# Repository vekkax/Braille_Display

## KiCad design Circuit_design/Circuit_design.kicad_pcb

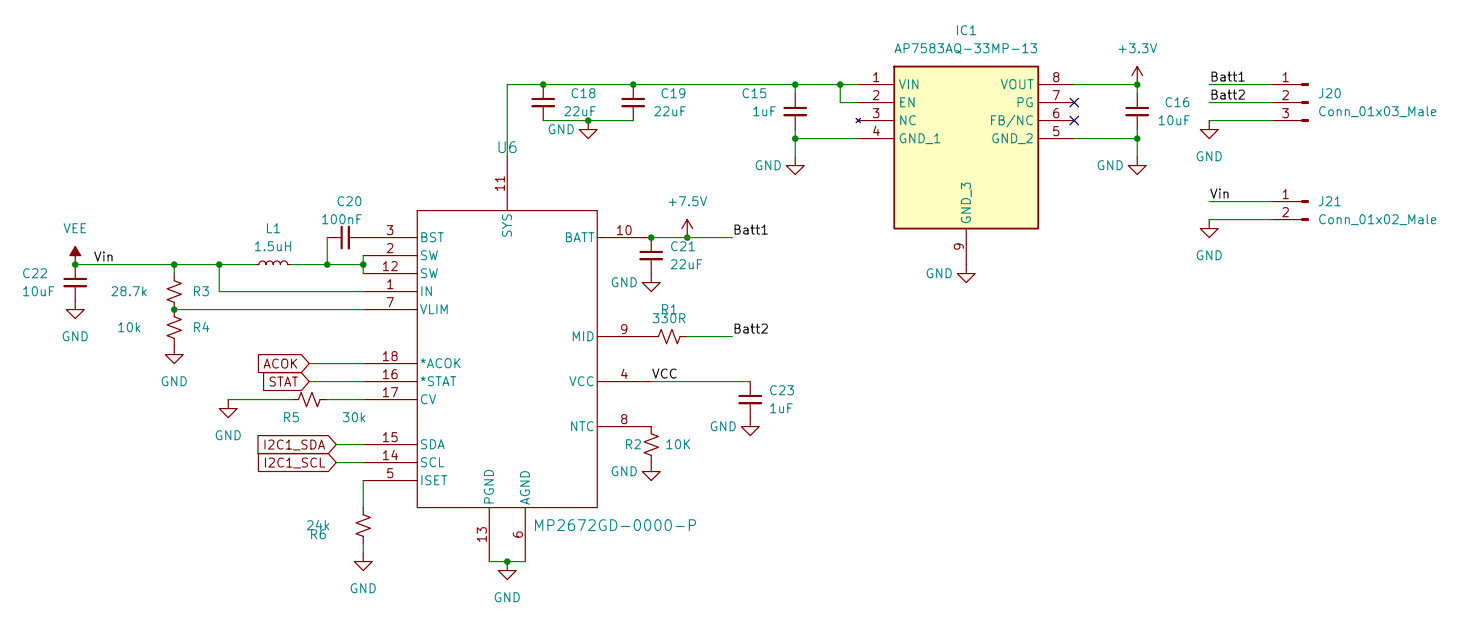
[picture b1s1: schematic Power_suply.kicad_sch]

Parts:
C15, C23: 1uF; C_0805_2012Metric_Pad1.18x1.45mm_HandSolder
C16, C22: 10uF; C_0805_2012Metric_Pad1.18x1.45mm_HandSolder
C18, C19, C21: 22uF; C_0805_2012Metric_Pad1.18x1.45mm_HandSolder
C20: 100nF; C_0805_2012Metric_Pad1.18x1.45mm_HandSolder
IC1: AP7583AQ-33MP-13; SOP65P490X110-9N; Mouser Part Number 621-AP7583AQ-33MP-13
J20: Conn_01x03_Male; JST_PH_S3B-PH-K_1x03_P2.00mm_Horizontal
J21: Conn_01x02_Male; JST_PH_S2B-PH-K_1x02_P2.00mm_Horizontal
L1: 1.5uH; L_Vishay_IHLP-2525
R1: 330R; R_0805_2012Metric_Pad1.20x1.40mm_HandSolder
R2: 10K; R_0805_2012Metric_Pad1.20x1.40mm_HandSolder
R3: 28.7k; R_0805_2012Metric_Pad1.20x1.40mm_HandSolder
R4: 10k; R_0805_2012Metric_Pad1.20x1.40mm_HandSolder
R5: 30k; R_0805_2012Metric_Pad1.20x1.40mm_HandSolder
R6: 24k; R_0805_2012Metric_Pad1.20x1.40mm_HandSolder
U6: MP2672GD-0000-P; QFN-18_2MMx3MM_MP2672_MNP_MPS

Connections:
+3.3V: C16.1, IC1.8 (VOUT); also elsewhere on the board
+7.5V: C21.1, J20.1, U6.10 (BATT); also elsewhere on the board
/Power_suply/Batt2: J20.2, R1.2
/Power_suply/VCC: C23.1, U6.4 (VCC)
ACOK: U6.18 (*ACOK)
GND: C15.2, C16.2, C18.2, C19.2, C21.2, C22.2, C23.2, IC1.4 (GND_1), IC1.5 (GND_2), IC1.9 (GND_3), J20.3, J21.2, R2.2, R4.1, R5.1, R6.1, U6.6 (AGND), U6.13 (PGND); also elsewhere on the board
I2C1_SCL: U6.14 (SCL); also elsewhere on the board
I2C1_SDA: U6.15 (SDA); also elsewhere on the board
unnamed: C20.1, L1.2, U6.2 (SW), U6.12 (SW)
unnamed: C15.1, C18.1, C19.1, IC1.1 (VIN), IC1.2 (EN), U6.11 (SYS)
unnamed: C20.2, U6.3 (BST)
unnamed: R5.2, U6.17 (CV)
unnamed: R6.2, U6.5 (ISET)
unnamed: R1.1, U6.9 (MID)
unnamed: R2.1, U6.8 (NTC)
unnamed: R3.1, R4.2, U6.7 (VLIM)
STAT: U6.16 (*STAT)
VEE: C22.1, J21.1, L1.1, R3.2, U6.1 (IN)

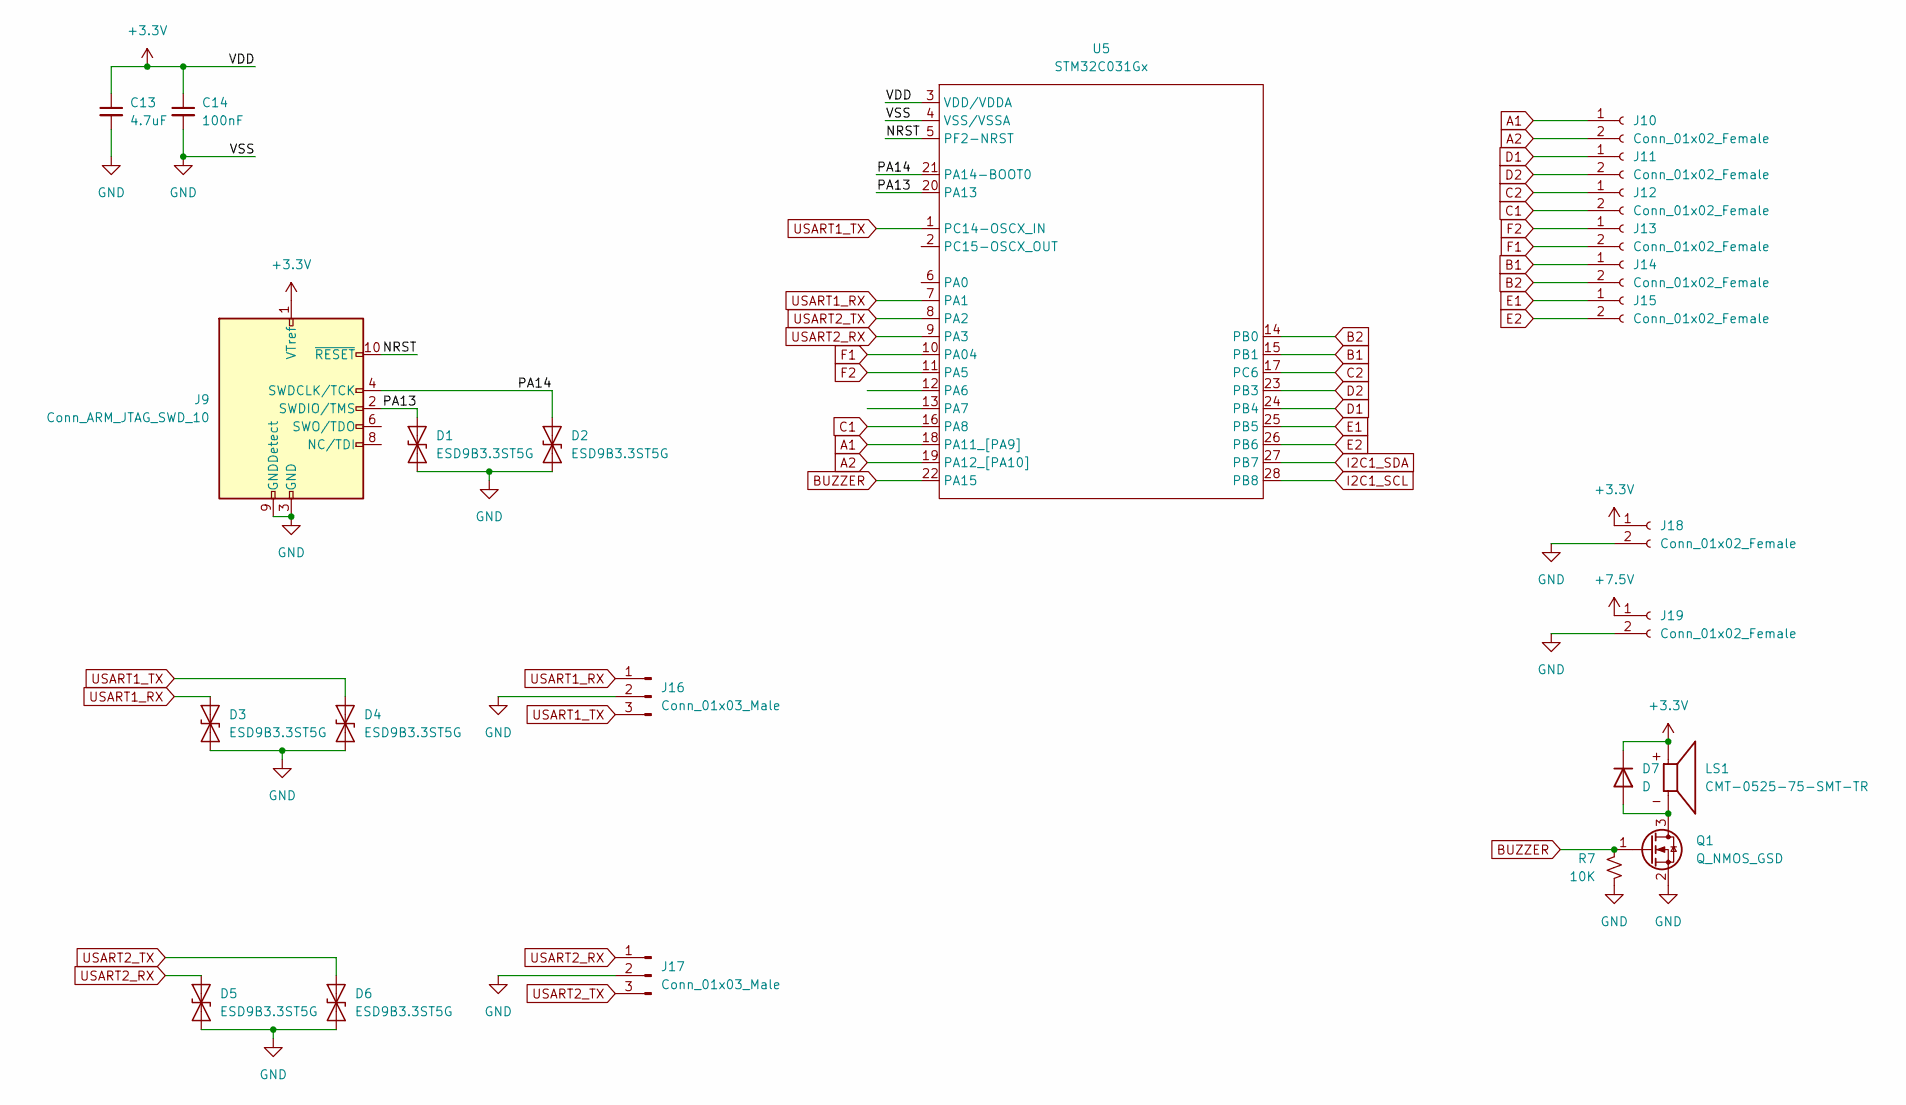
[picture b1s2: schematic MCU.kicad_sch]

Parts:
C13: 4.7uF; C_0603_1608Metric_Pad1.08x0.95mm_HandSolder
C14: 100nF; C_0603_1608Metric_Pad1.08x0.95mm_HandSolder
D1, D2, D3, D4, D5, D6: ESD9B3.3ST5G; D_SOD-923
D7: D; D_SOD-323
J9: Conn_ARM_JTAG_SWD_10; PinHeader_2x05_P1.27mm_Vertical
J10, J11, J12, J13, J14, J15, J18, J19: Conn_01x02_Female; PinSocket_1x02_P2.54mm_Vertical
J16, J17: Conn_01x03_Male; JST_PH_S3B-PH-K_1x03_P2.00mm_Horizontal
LS1: CMT-0525-75-SMT-TR; XDCR_CMT-0525-75-SMT-TR; PARTREV 1.0
Q1: Q_NMOS_GSD; SOT-23-3
R7: 10K; R_0805_2012Metric_Pad1.20x1.40mm_HandSolder
U5: STM32C031Gx; QFN50P400X400X60-28N

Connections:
+3.3V: C13.1, C14.1, D7.1 (K), J9.1 (VTref), J18.1, LS1.P, U5.3 (VDD/VDDA); also elsewhere on the board
+7.5V: J19.1; also elsewhere on the board
/MCU/NRST: J9.10 (~RESET), U5.5 (PF2-NRST)
/MCU/PA13: D1.2 (A2), J9.2 (SWDIO/TMS), U5.20 (PA13)
/MCU/PA14: D2.2 (A2), J9.4 (SWDCLK/TCK), U5.21 (PA14-BOOT0)
A1: J10.1, U5.18 (PA11_[PA9]); also elsewhere on the board
A2: J10.2, U5.19 (PA12_[PA10]); also elsewhere on the board
B1: J14.1, U5.15 (PB1); also elsewhere on the board
B2: J14.2, U5.14 (PB0); also elsewhere on the board
BUZZER: Q1.1 (G), R7.1, U5.22 (PA15)
C1: J12.2, U5.16 (PA8); also elsewhere on the board
C2: J12.1, U5.17 (PC6); also elsewhere on the board
D1: J11.1, U5.24 (PB4); also elsewhere on the board
D2: J11.2, U5.23 (PB3); also elsewhere on the board
E1: J15.1, U5.25 (PB5); also elsewhere on the board
E2: J15.2, U5.26 (PB6); also elsewhere on the board
F1: J13.2, U5.10 (PA04); also elsewhere on the board
F2: J13.1, U5.11 (PA5); also elsewhere on the board
GND: C13.2, C14.2, D1.1 (A1), D2.1 (A1), D3.1 (A1), D4.1 (A1), D5.1 (A1), D6.1 (A1), J9.3 (GND), J9.5 (GND), J9.9 (GNDDetect), J16.2, J17.2, J18.2, J19.2, Q1.2 (S), R7.2, U5.4 (VSS/VSSA); also elsewhere on the board
I2C1_SCL: U5.28 (PB8); also elsewhere on the board
I2C1_SDA: U5.27 (PB7); also elsewhere on the board
unnamed: D7.2 (A), LS1.N, Q1.3 (D)
USART1_RX: D3.2 (A2), J16.1, U5.7 (PA1)
USART1_TX: D4.2 (A2), J16.3, U5.1 (PC14-OSCX_IN)
USART2_RX: D5.2 (A2), J17.1, U5.9 (PA3)
USART2_TX: D6.2 (A2), J17.3, U5.8 (PA2)

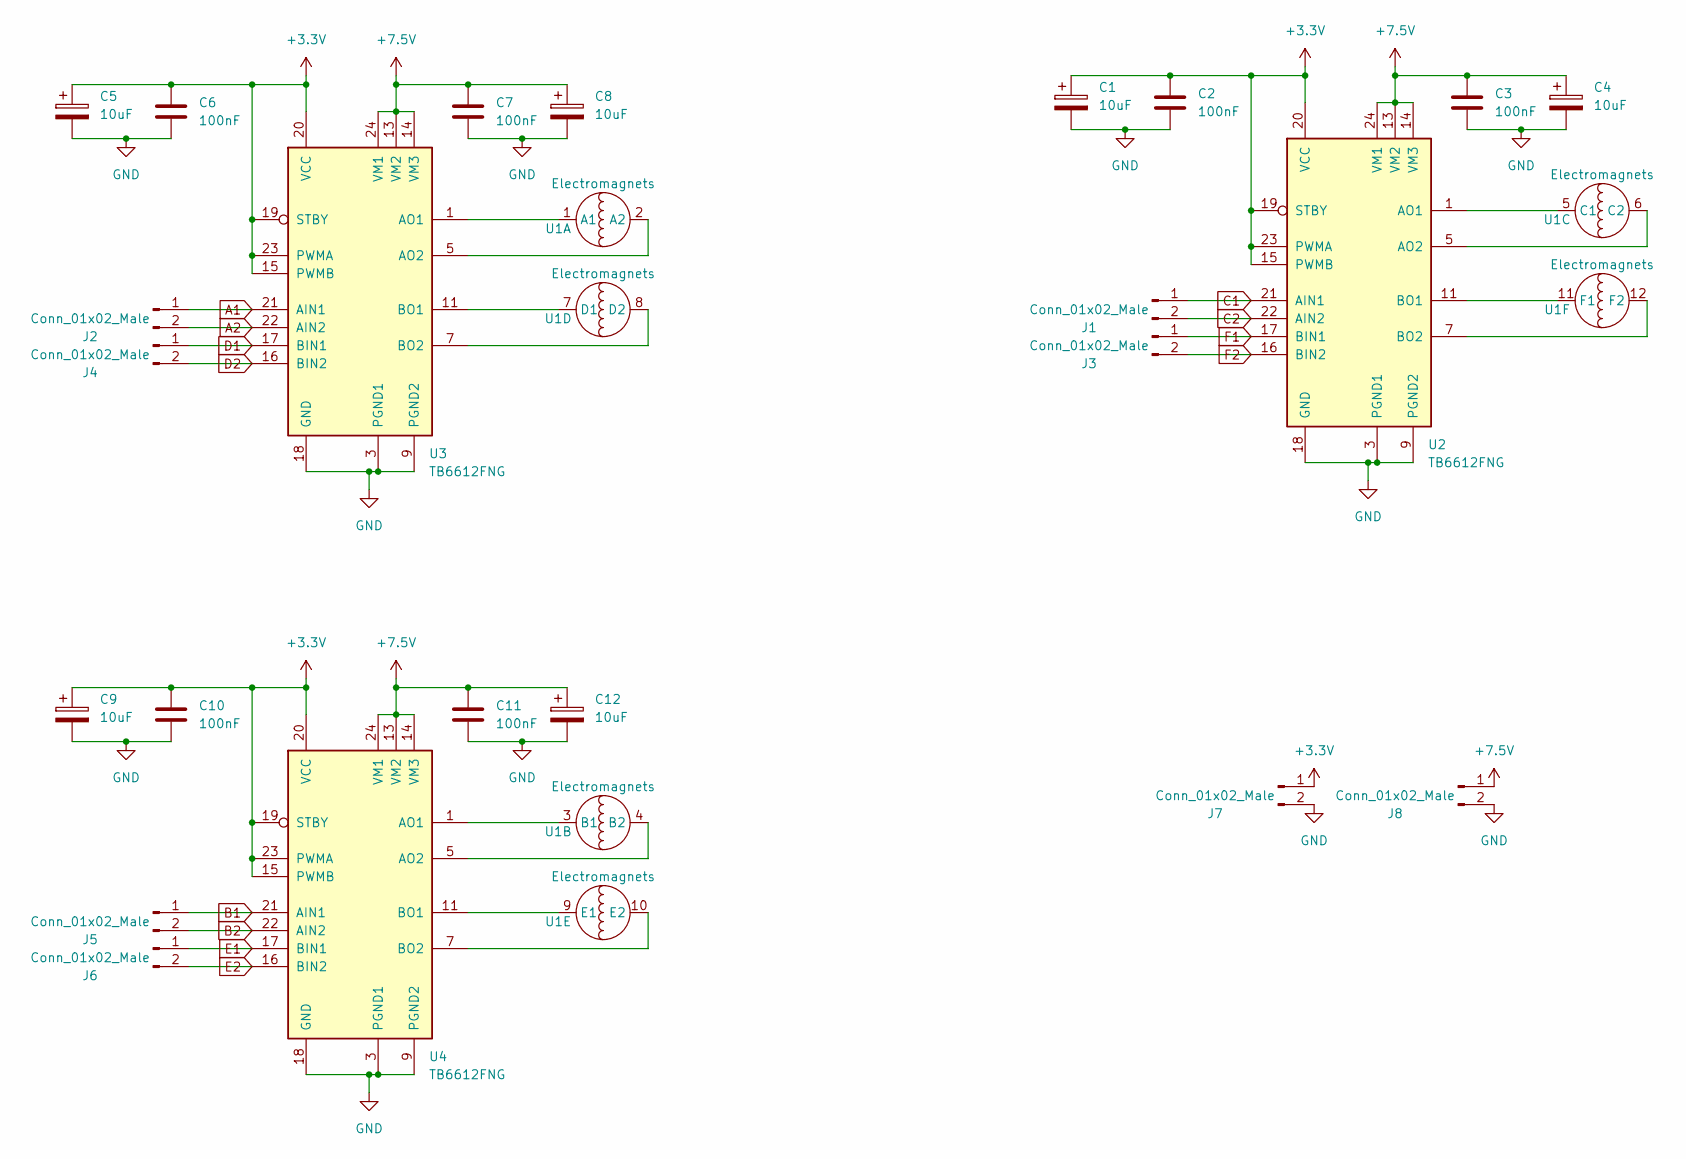
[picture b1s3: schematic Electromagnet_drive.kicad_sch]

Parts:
C1, C4, C5, C8, C9, C12: 10uF; C_0603_1608Metric_Pad1.08x0.95mm_HandSolder
C2, C3, C6, C7, C10, C11: 100nF; C_0603_1608Metric_Pad1.08x0.95mm_HandSolder
J1, J2, J3, J4, J5, J6, J7, J8: Conn_01x02_Male; PinHeader_1x02_P2.54mm_Vertical
U1: Electromagnets
U2, U3, U4: TB6612FNG; SSOP-24_5.3x8.2mm_P0.65mm

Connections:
+3.3V: C1.1, C2.1, C5.1, C6.1, C9.1, C10.1, J7.1, U2.15 (PWMB), U2.19 (STBY), U2.20 (VCC), U2.23 (PWMA), U3.15 (PWMB), U3.19 (STBY), U3.20 (VCC), U3.23 (PWMA), U4.15 (PWMB), U4.19 (STBY), U4.20 (VCC), U4.23 (PWMA); also elsewhere on the board
+7.5V: C3.1, C4.1, C7.1, C8.1, C11.1, C12.1, J8.1, U2.13 (VM2), U2.14 (VM3), U2.24 (VM1), U3.13 (VM2), U3.14 (VM3), U3.24 (VM1), U4.13 (VM2), U4.14 (VM3), U4.24 (VM1); also elsewhere on the board
A1: J2.1, U3.21 (AIN1); also elsewhere on the board
A2: J2.2, U3.22 (AIN2); also elsewhere on the board
B1: J5.1, U4.21 (AIN1); also elsewhere on the board
B2: J5.2, U4.22 (AIN2); also elsewhere on the board
C1: J1.1, U2.21 (AIN1); also elsewhere on the board
C2: J1.2, U2.22 (AIN2); also elsewhere on the board
D1: J4.1, U3.17 (BIN1); also elsewhere on the board
D2: J4.2, U3.16 (BIN2); also elsewhere on the board
E1: J6.1, U4.17 (BIN1); also elsewhere on the board
E2: J6.2, U4.16 (BIN2); also elsewhere on the board
F1: J3.1, U2.17 (BIN1); also elsewhere on the board
F2: J3.2, U2.16 (BIN2); also elsewhere on the board
GND: C1.2, C2.2, C3.2, C4.2, C5.2, C6.2, C7.2, C8.2, C9.2, C10.2, C11.2, C12.2, J7.2, J8.2, U2.3 (PGND1), U2.4 (PGND1), U2.9 (PGND2), U2.10 (PGND2), U2.18 (GND), U3.3 (PGND1), U3.4 (PGND1), U3.9 (PGND2), U3.10 (PGND2), U3.18 (GND), U4.3 (PGND1), U4.4 (PGND1), U4.9 (PGND2), U4.10 (PGND2), U4.18 (GND); also elsewhere on the board
unnamed: U1.1 (A1), U3.1 (AO1), U3.2 (AO1)
unnamed: U1.2 (A2), U3.5 (AO2), U3.6 (AO2)
unnamed: U1.3 (B1), U4.1 (AO1), U4.2 (AO1)
unnamed: U1.4 (B2), U4.5 (AO2), U4.6 (AO2)
unnamed: U1.5 (C1), U2.1 (AO1), U2.2 (AO1)
unnamed: U1.6 (C2), U2.5 (AO2), U2.6 (AO2)
unnamed: U1.7 (D1), U3.11 (BO1), U3.12 (BO1)
unnamed: U1.8 (D2), U3.7 (BO2), U3.8 (BO2)
unnamed: U1.9 (E1), U4.11 (BO1), U4.12 (BO1)
unnamed: U1.10 (E2), U4.7 (BO2), U4.8 (BO2)
unnamed: U1.11 (F1), U2.11 (BO1), U2.12 (BO1)
unnamed: U1.12 (F2), U2.7 (BO2), U2.8 (BO2)

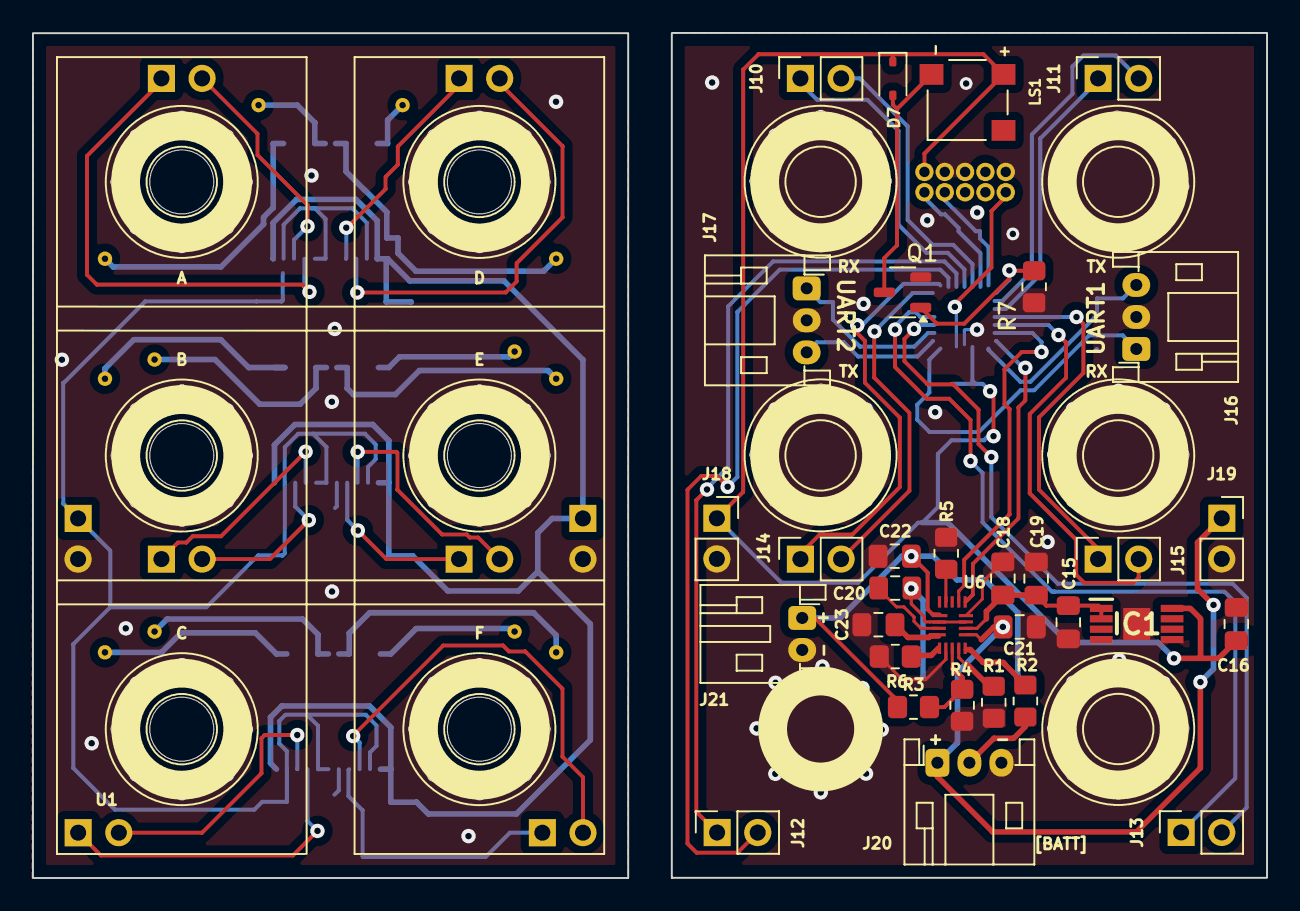
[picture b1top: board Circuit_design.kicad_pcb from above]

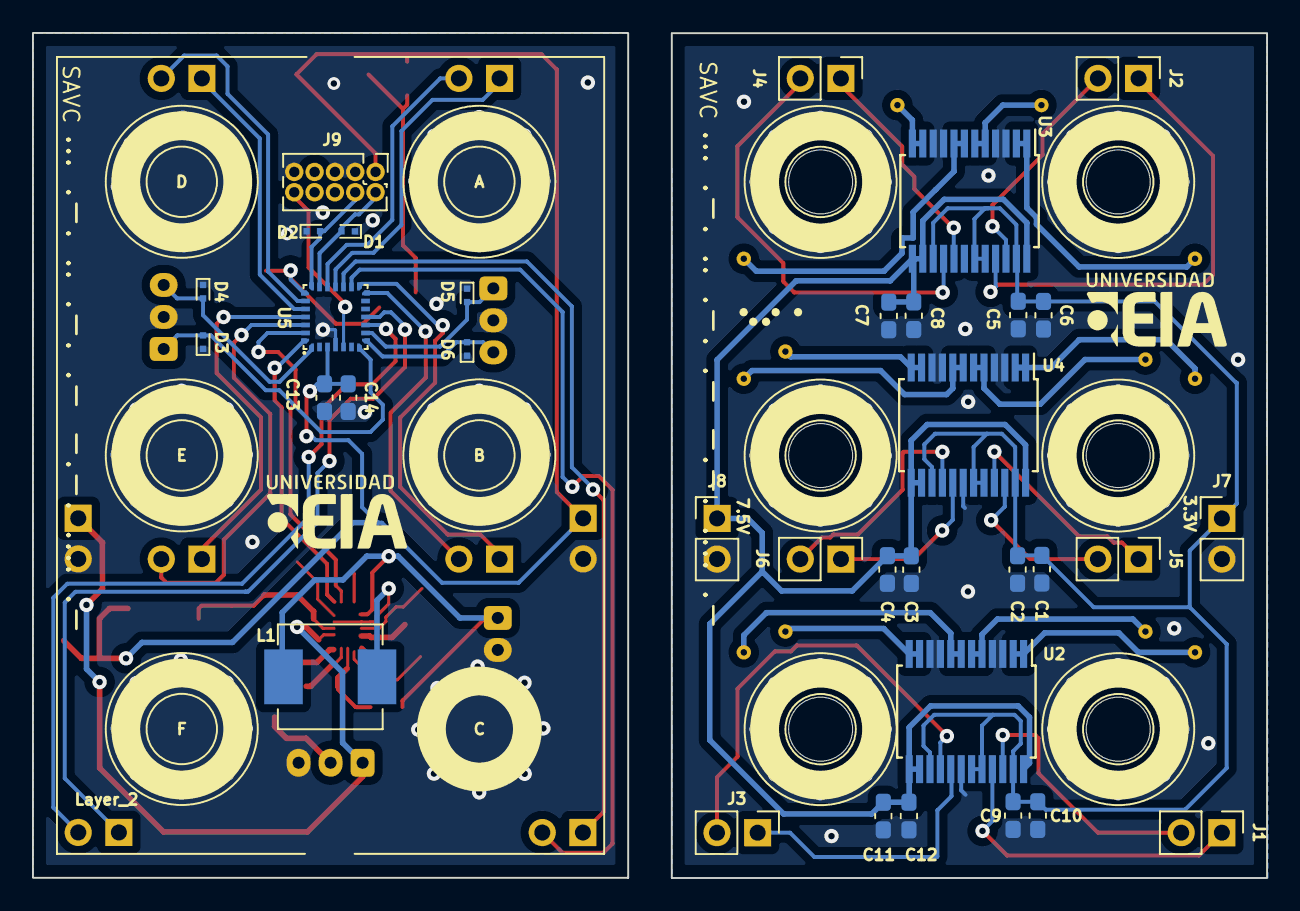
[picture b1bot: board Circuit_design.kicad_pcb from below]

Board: 2 copper layers, 77.1 x 52.8 mm, 68 parts (35 on the bottom side), 49 nets.

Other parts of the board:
Layer_2: Electromagnets_Layer_2

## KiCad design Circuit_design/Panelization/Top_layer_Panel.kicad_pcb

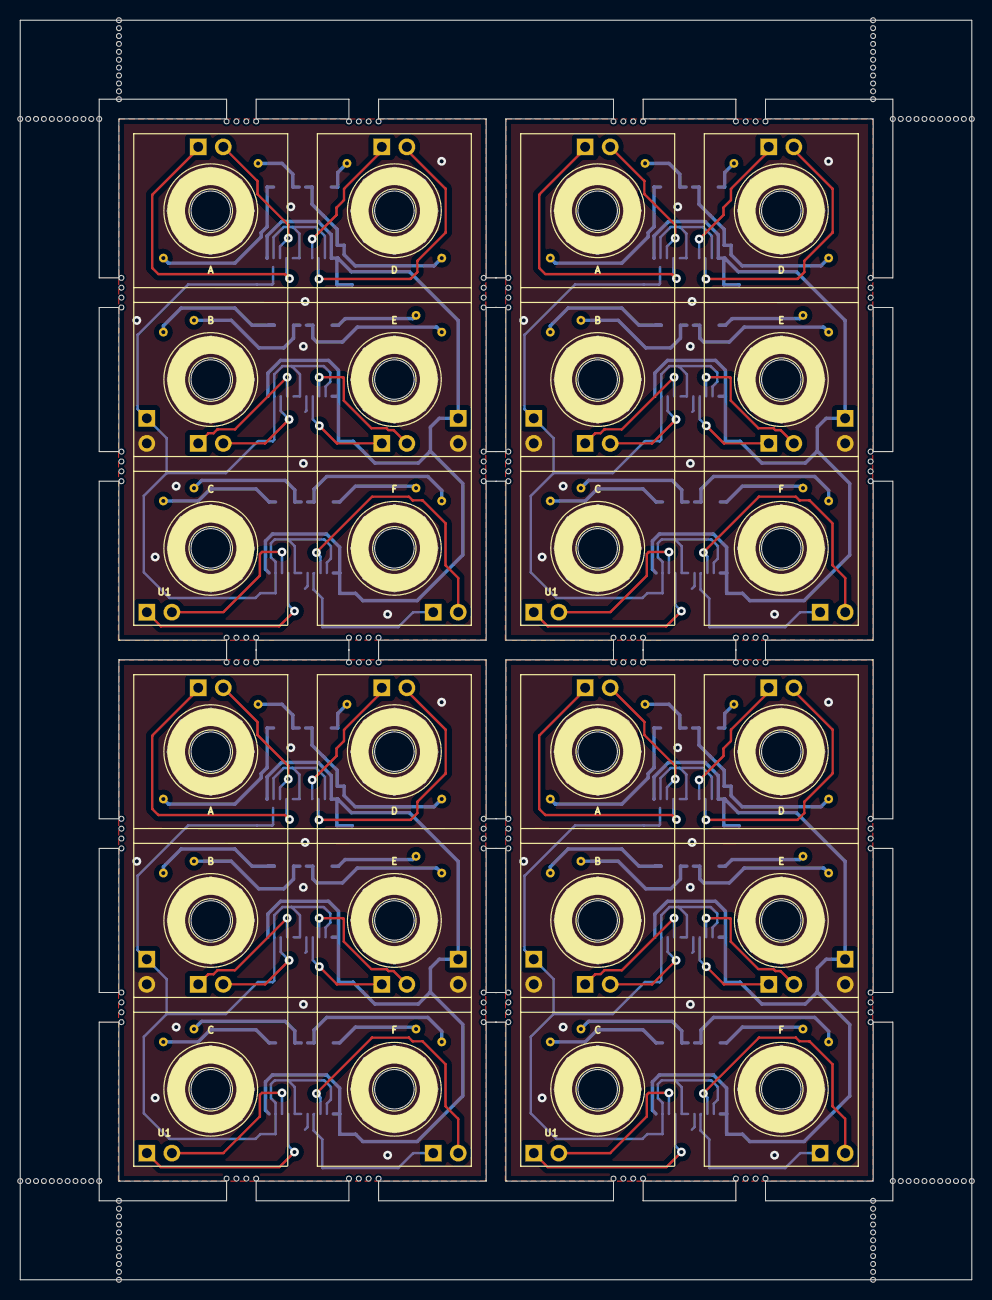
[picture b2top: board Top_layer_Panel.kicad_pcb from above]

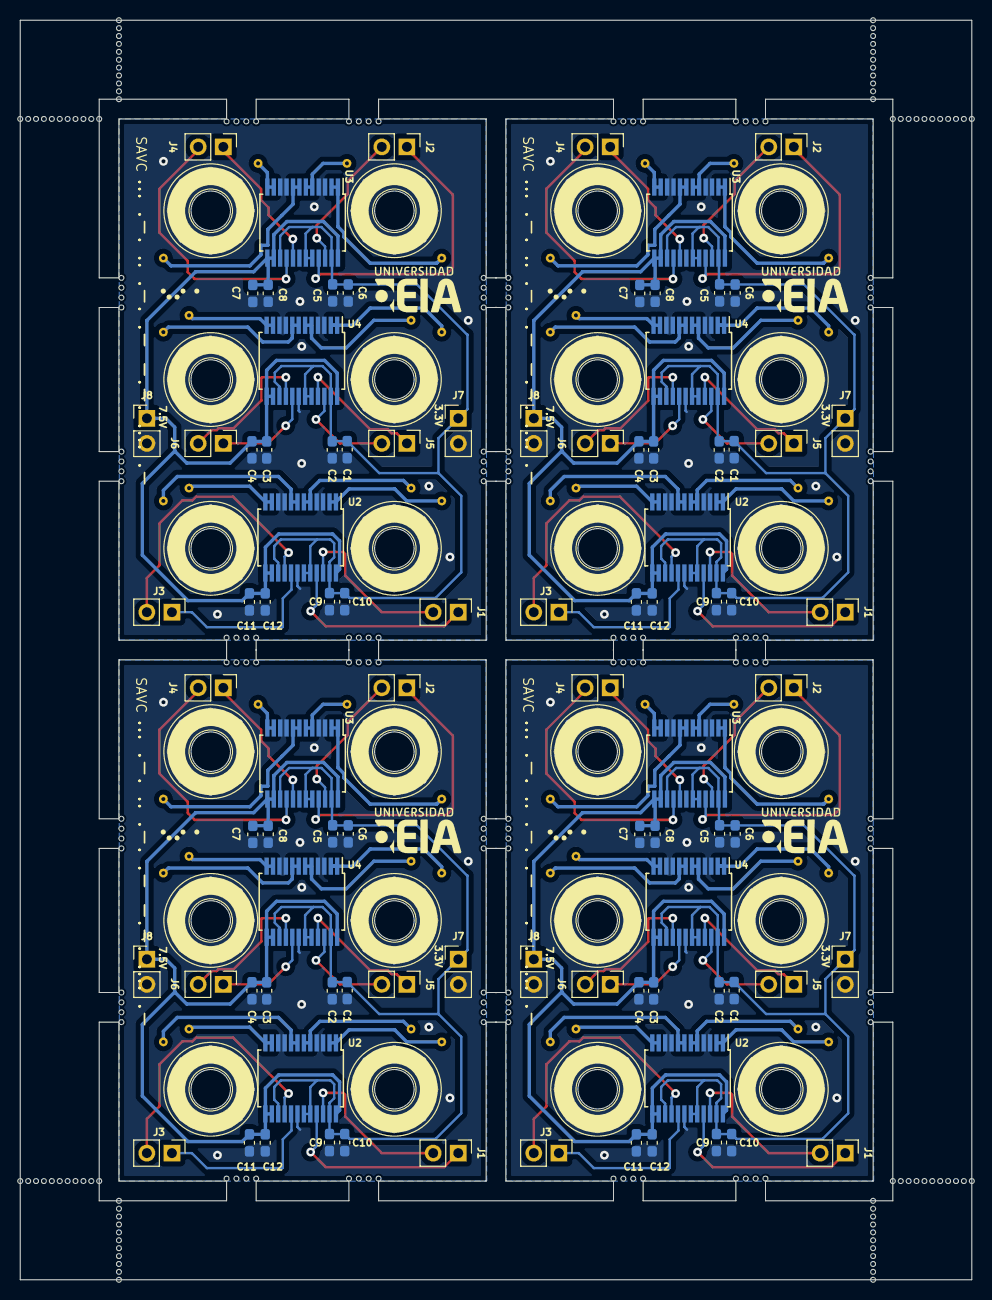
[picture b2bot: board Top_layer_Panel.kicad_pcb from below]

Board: 2 copper layers, 96.4 x 127.6 mm, 312 parts (92 on the bottom side), 108 nets.

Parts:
C1, C1#2, C1#3, C1#4, C4, C4#2, C4#3, C4#4, C5, C5#2, C5#3, C5#4, C8, C8#2, C8#3, C8#4, C9, C9#2, C9#3, C9#4, C12, C12#2, C12#3, C12#4: 10uF; C_0603_1608Metric_Pad1.08x0.95mm_HandSolder
C2, C2#2, C2#3, C2#4, C3, C3#2, C3#3, C3#4, C6, C6#2, C6#3, C6#4, C7, C7#2, C7#3, C7#4, C10, C10#2, C10#3, C10#4, C11, C11#2, C11#3, C11#4: 100nF; C_0603_1608Metric_Pad1.08x0.95mm_HandSolder
J1, J1#2, J1#3, J1#4, J2, J2#2, J2#3, J2#4, J3, J3#2, J3#3, J3#4, J4, J4#2, J4#3, J4#4, J5, J5#2, J5#3, J5#4, J6, J6#2, J6#3, J6#4, J7, J7#2, J7#3, J7#4, J8, J8#2, J8#3, J8#4: Conn_01x02_Male; PinHeader_1x02_P2.54mm_Vertical
KiKit_MB_1_1, KiKit_MB_1_2, KiKit_MB_1_3, KiKit_MB_1_4, KiKit_MB_2_1, KiKit_MB_2_2, KiKit_MB_2_3, KiKit_MB_2_4, KiKit_MB_3_1, KiKit_MB_3_2, KiKit_MB_3_3, KiKit_MB_3_4, KiKit_MB_4_1, KiKit_MB_4_2, KiKit_MB_4_3, KiKit_MB_4_4, KiKit_MB_5_1, KiKit_MB_5_2, KiKit_MB_5_3, KiKit_MB_5_4, KiKit_MB_6_1, KiKit_MB_6_2, KiKit_MB_6_3, KiKit_MB_6_4, KiKit_MB_7_1, KiKit_MB_7_2, KiKit_MB_7_3, KiKit_MB_7_4, KiKit_MB_8_1, KiKit_MB_8_2, KiKit_MB_8_3, KiKit_MB_8_4, KiKit_MB_9_1, KiKit_MB_9_2, KiKit_MB_9_3, KiKit_MB_9_4, KiKit_MB_10_1, KiKit_MB_10_2, KiKit_MB_10_3, KiKit_MB_10_4, KiKit_MB_11_1, KiKit_MB_11_2, KiKit_MB_11_3, KiKit_MB_11_4, KiKit_MB_12_1, KiKit_MB_12_2, KiKit_MB_12_3, KiKit_MB_12_4, KiKit_MB_13_1, KiKit_MB_13_2, KiKit_MB_13_3, KiKit_MB_13_4, KiKit_MB_14_1, KiKit_MB_14_2, KiKit_MB_14_3, KiKit_MB_14_4, KiKit_MB_15_1, KiKit_MB_15_2, KiKit_MB_15_3, KiKit_MB_15_4, KiKit_MB_16_1, KiKit_MB_16_2, KiKit_MB_16_3, KiKit_MB_16_4, KiKit_MB_17_1, KiKit_MB_17_2, KiKit_MB_17_3, KiKit_MB_17_4, KiKit_MB_18_1, KiKit_MB_18_2, KiKit_MB_18_3, KiKit_MB_18_4, KiKit_MB_19_1, KiKit_MB_19_2, KiKit_MB_19_3, KiKit_MB_19_4, KiKit_MB_20_1, KiKit_MB_20_2, KiKit_MB_20_3, KiKit_MB_20_4, KiKit_MB_21_1, KiKit_MB_21_2, KiKit_MB_21_3, KiKit_MB_21_4, KiKit_MB_22_1, KiKit_MB_22_2, KiKit_MB_22_3, KiKit_MB_22_4, KiKit_MB_23_1, KiKit_MB_23_2, KiKit_MB_23_3, KiKit_MB_23_4, KiKit_MB_24_1, KiKit_MB_24_2, KiKit_MB_24_3, KiKit_MB_24_4, KiKit_MB_25_1, KiKit_MB_25_2, KiKit_MB_25_3, KiKit_MB_25_4, KiKit_MB_26_1, KiKit_MB_26_2, KiKit_MB_26_3, KiKit_MB_26_4, KiKit_MB_27_1, KiKit_MB_27_2, KiKit_MB_27_3, KiKit_MB_27_4, KiKit_MB_28_1, KiKit_MB_28_2, KiKit_MB_28_3, KiKit_MB_28_4, KiKit_MB_29_1, KiKit_MB_29_2, KiKit_MB_29_3, KiKit_MB_29_4, KiKit_MB_30_1, KiKit_MB_30_2, KiKit_MB_30_3, KiKit_MB_30_4, KiKit_MB_31_1, KiKit_MB_31_2, KiKit_MB_31_3, KiKit_MB_31_4, KiKit_MB_32_1, KiKit_MB_32_2, KiKit_MB_32_3, KiKit_MB_32_4, KiKit_MB_33_1, KiKit_MB_33_2, KiKit_MB_33_3, KiKit_MB_33_4, KiKit_MB_33_5, KiKit_MB_33_6, KiKit_MB_33_7, KiKit_MB_33_8, KiKit_MB_33_9, KiKit_MB_33_10, KiKit_MB_33_11, KiKit_MB_34_1, KiKit_MB_34_2, KiKit_MB_34_3, KiKit_MB_34_4, KiKit_MB_34_5, KiKit_MB_34_6, KiKit_MB_34_7, KiKit_MB_34_8, KiKit_MB_34_9, KiKit_MB_34_10, KiKit_MB_34_11, KiKit_MB_35_1, KiKit_MB_35_2, KiKit_MB_35_3, KiKit_MB_35_4, KiKit_MB_35_5, KiKit_MB_35_6, KiKit_MB_35_7, KiKit_MB_35_8, KiKit_MB_35_9, KiKit_MB_35_10, KiKit_MB_35_11, KiKit_MB_36_1, KiKit_MB_36_2, KiKit_MB_36_3, KiKit_MB_36_4, KiKit_MB_36_5, KiKit_MB_36_6, KiKit_MB_36_7, KiKit_MB_36_8, KiKit_MB_36_9, KiKit_MB_36_10, KiKit_MB_36_11, KiKit_MB_37_1, KiKit_MB_37_2, KiKit_MB_37_3, KiKit_MB_37_4, KiKit_MB_37_5, KiKit_MB_37_6, KiKit_MB_37_7, KiKit_MB_37_8, KiKit_MB_37_9, KiKit_MB_37_10, KiKit_MB_37_11, KiKit_MB_38_1, KiKit_MB_38_2, KiKit_MB_38_3, KiKit_MB_38_4, KiKit_MB_38_5, KiKit_MB_38_6, KiKit_MB_38_7, KiKit_MB_38_8, KiKit_MB_38_9, KiKit_MB_38_10, KiKit_MB_38_11, KiKit_MB_39_1, KiKit_MB_39_2, KiKit_MB_39_3, KiKit_MB_39_4, KiKit_MB_39_5, KiKit_MB_39_6, KiKit_MB_39_7, KiKit_MB_39_8, KiKit_MB_39_9, KiKit_MB_39_10, KiKit_MB_39_11, KiKit_MB_40_1, KiKit_MB_40_2, KiKit_MB_40_3, KiKit_MB_40_4, KiKit_MB_40_5, KiKit_MB_40_6, KiKit_MB_40_7, KiKit_MB_40_8, KiKit_MB_40_9, KiKit_MB_40_10, KiKit_MB_40_11: NPTH
U1, U1#2, U1#3, U1#4: Electromagnets
U2, U2#2, U2#3, U2#4, U3, U3#2, U3#3, U3#4, U4, U4#2, U4#3, U4#4: TB6612FNG; SSOP-24_5.3x8.2mm_P0.65mm

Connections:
Board_0-+3.3V: C1#4.1, C2.1, C5.1, C6#3.1, C9#2.1, C10.1, J7#3.1, U2#3.15 (PWMB), U2#3.19 (STBY), U2#3.20 (VCC), U2#3.23 (PWMA), U3#3.15 (PWMB), U3#3.19 (STBY), U3#3.20 (VCC), U3#3.23 (PWMA), U4#2.15 (PWMB), U4#2.19 (STBY), U4#2.20 (VCC), U4#2.23 (PWMA)
Board_0-+7.5V: C3#2.1, C4#2.1, C7#2.1, C8#2.1, C11#2.1, C12#2.1, J8#4.1, U2#3.13 (VM2), U2#3.14 (VM3), U2#3.24 (VM1), U3#3.13 (VM2), U3#3.14 (VM3), U3#3.24 (VM1), U4#2.13 (VM2), U4#2.14 (VM3), U4#2.24 (VM1)
Board_0-A1: J2#4.1, U3#3.21 (AIN1)
Board_0-A2: J2#4.2, U3#3.22 (AIN2)
Board_0-B1: J5#3.1, U4#2.21 (AIN1)
Board_0-B2: J5#3.2, U4#2.22 (AIN2)
Board_0-C1: J1#4.1, U2#3.21 (AIN1)
Board_0-C2: J1#4.2, U2#3.22 (AIN2)
Board_0-D1: J4#4.1, U3#3.17 (BIN1)
Board_0-D2: J4#4.2, U3#3.16 (BIN2)
Board_0-E1: J6.1, U4#2.17 (BIN1)
Board_0-E2: J6.2, U4#2.16 (BIN2)
Board_0-F1: J3#4.1, U2#3.17 (BIN1)
Board_0-F2: J3#4.2, U2#3.16 (BIN2)
Board_0-GND: C1#4.2, C2.2, C3#2.2, C4#2.2, C5.2, C6#3.2, C7#2.2, C8#2.2, C9#2.2, C10.2, C11#2.2, C12#2.2, J7#3.2, J8#4.2, U2#3.3 (PGND1), U2#3.4 (PGND1), U2#3.9 (PGND2), U2#3.10 (PGND2), U2#3.18 (GND), U3#3.3 (PGND1), U3#3.4 (PGND1), U3#3.9 (PGND2), U3#3.10 (PGND2), U3#3.18 (GND), U4#2.3 (PGND1), U4#2.4 (PGND1), U4#2.9 (PGND2), U4#2.10 (PGND2), U4#2.18 (GND)
Board_0-Net-(U1A-A1): U1#3.1 (A1), U3#3.1 (AO1), U3#3.2 (AO1)
Board_0-Net-(U1A-A2): U1#3.2 (A2), U3#3.5 (AO2), U3#3.6 (AO2)
Board_0-Net-(U1B-B1): U1#3.3 (B1), U4#2.1 (AO1), U4#2.2 (AO1)
Board_0-Net-(U1B-B2): U1#3.4 (B2), U4#2.5 (AO2), U4#2.6 (AO2)
Board_0-Net-(U1C-C1): U1#3.5 (C1), U2#3.1 (AO1), U2#3.2 (AO1)
Board_0-Net-(U1C-C2): U1#3.6 (C2), U2#3.5 (AO2), U2#3.6 (AO2)
Board_0-Net-(U1D-D1): U1#3.7 (D1), U3#3.11 (BO1), U3#3.12 (BO1)
Board_0-Net-(U1D-D2): U1#3.8 (D2), U3#3.7 (BO2), U3#3.8 (BO2)
Board_0-Net-(U1E-E1): U1#3.9 (E1), U4#2.11 (BO1), U4#2.12 (BO1)
Board_0-Net-(U1E-E2): U1#3.10 (E2), U4#2.7 (BO2), U4#2.8 (BO2)
Board_0-Net-(U1F-F1): U1#3.11 (F1), U2#3.11 (BO1), U2#3.12 (BO1)
Board_0-Net-(U1F-F2): U1#3.12 (F2), U2#3.7 (BO2), U2#3.8 (BO2)
Board_1-+3.3V: C1#2.1, C2#4.1, C5#4.1, C6.1, C9#4.1, C10#3.1, J7.1, U2#4.15 (PWMB), U2#4.19 (STBY), U2#4.20 (VCC), U2#4.23 (PWMA), U3#4.15 (PWMB), U3#4.19 (STBY), U3#4.20 (VCC), U3#4.23 (PWMA), U4.15 (PWMB), U4.19 (STBY), U4.20 (VCC), U4.23 (PWMA)
Board_1-+7.5V: C3#4.1, C4#4.1, C7#3.1, C8.1, C11#4.1, C12#3.1, J8#2.1, U2#4.13 (VM2), U2#4.14 (VM3), U2#4.24 (VM1), U3#4.13 (VM2), U3#4.14 (VM3), U3#4.24 (VM1), U4.13 (VM2), U4.14 (VM3), U4.24 (VM1)
Board_1-A1: J2.1, U3#4.21 (AIN1)
Board_1-A2: J2.2, U3#4.22 (AIN2)
Board_1-B1: J5#4.1, U4.21 (AIN1)
Board_1-B2: J5#4.2, U4.22 (AIN2)
Board_1-C1: J1#3.1, U2#4.21 (AIN1)
Board_1-C2: J1#3.2, U2#4.22 (AIN2)
Board_1-D1: J4#2.1, U3#4.17 (BIN1)
Board_1-D2: J4#2.2, U3#4.16 (BIN2)
Board_1-E1: J6#2.1, U4.17 (BIN1)
Board_1-E2: J6#2.2, U4.16 (BIN2)
Board_1-F1: J3#3.1, U2#4.17 (BIN1)
Board_1-F2: J3#3.2, U2#4.16 (BIN2)
Board_1-GND: C1#2.2, C2#4.2, C3#4.2, C4#4.2, C5#4.2, C6.2, C7#3.2, C8.2, C9#4.2, C10#3.2, C11#4.2, C12#3.2, J7.2, J8#2.2, U2#4.3 (PGND1), U2#4.4 (PGND1), U2#4.9 (PGND2), U2#4.10 (PGND2), U2#4.18 (GND), U3#4.3 (PGND1), U3#4.4 (PGND1), U3#4.9 (PGND2), U3#4.10 (PGND2), U3#4.18 (GND), U4.3 (PGND1), U4.4 (PGND1), U4.9 (PGND2), U4.10 (PGND2), U4.18 (GND)
Board_1-Net-(U1A-A1): U1#4.1 (A1), U3#4.1 (AO1), U3#4.2 (AO1)
Board_1-Net-(U1A-A2): U1#4.2 (A2), U3#4.5 (AO2), U3#4.6 (AO2)
Board_1-Net-(U1B-B1): U1#4.3 (B1), U4.1 (AO1), U4.2 (AO1)
Board_1-Net-(U1B-B2): U1#4.4 (B2), U4.5 (AO2), U4.6 (AO2)
Board_1-Net-(U1C-C1): U1#4.5 (C1), U2#4.1 (AO1), U2#4.2 (AO1)
Board_1-Net-(U1C-C2): U1#4.6 (C2), U2#4.5 (AO2), U2#4.6 (AO2)
Board_1-Net-(U1D-D1): U1#4.7 (D1), U3#4.11 (BO1), U3#4.12 (BO1)
Board_1-Net-(U1D-D2): U1#4.8 (D2), U3#4.7 (BO2), U3#4.8 (BO2)
Board_1-Net-(U1E-E1): U1#4.9 (E1), U4.11 (BO1), U4.12 (BO1)
Board_1-Net-(U1E-E2): U1#4.10 (E2), U4.7 (BO2), U4.8 (BO2)
Board_1-Net-(U1F-F1): U1#4.11 (F1), U2#4.11 (BO1), U2#4.12 (BO1)
Board_1-Net-(U1F-F2): U1#4.12 (F2), U2#4.7 (BO2), U2#4.8 (BO2)
Board_2-+3.3V: C1.1, C2#3.1, C5#2.1, C6#4.1, C9#3.1, C10#4.1, J7#4.1, U2#2.15 (PWMB), U2#2.19 (STBY), U2#2.20 (VCC), U2#2.23 (PWMA), U3#2.15 (PWMB), U3#2.19 (STBY), U3#2.20 (VCC), U3#2.23 (PWMA), U4#4.15 (PWMB), U4#4.19 (STBY), U4#4.20 (VCC), U4#4.23 (PWMA)
Board_2-+7.5V: C3#3.1, C4.1, C7.1, C8#4.1, C11#3.1, C12.1, J8#3.1, U2#2.13 (VM2), U2#2.14 (VM3), U2#2.24 (VM1), U3#2.13 (VM2), U3#2.14 (VM3), U3#2.24 (VM1), U4#4.13 (VM2), U4#4.14 (VM3), U4#4.24 (VM1)
Board_2-A1: J2#2.1, U3#2.21 (AIN1)
Board_2-A2: J2#2.2, U3#2.22 (AIN2)
Board_2-B1: J5#2.1, U4#4.21 (AIN1)
Board_2-B2: J5#2.2, U4#4.22 (AIN2)
Board_2-C1: J1#2.1, U2#2.21 (AIN1)
Board_2-C2: J1#2.2, U2#2.22 (AIN2)
Board_2-D1: J4#3.1, U3#2.17 (BIN1)
Board_2-D2: J4#3.2, U3#2.16 (BIN2)
Board_2-E1: J6#3.1, U4#4.17 (BIN1)
Board_2-E2: J6#3.2, U4#4.16 (BIN2)
Board_2-F1: J3#2.1, U2#2.17 (BIN1)
Board_2-F2: J3#2.2, U2#2.16 (BIN2)
Board_2-GND: C1.2, C2#3.2, C3#3.2, C4.2, C5#2.2, C6#4.2, C7.2, C8#4.2, C9#3.2, C10#4.2, C11#3.2, C12.2, J7#4.2, J8#3.2, U2#2.3 (PGND1), U2#2.4 (PGND1), U2#2.9 (PGND2), U2#2.10 (PGND2), U2#2.18 (GND), U3#2.3 (PGND1), U3#2.4 (PGND1), U3#2.9 (PGND2), U3#2.10 (PGND2), U3#2.18 (GND), U4#4.3 (PGND1), U4#4.4 (PGND1), U4#4.9 (PGND2), U4#4.10 (PGND2), U4#4.18 (GND)
Board_2-Net-(U1A-A1): U1.1 (A1), U3#2.1 (AO1), U3#2.2 (AO1)
Board_2-Net-(U1A-A2): U1.2 (A2), U3#2.5 (AO2), U3#2.6 (AO2)
Board_2-Net-(U1B-B1): U1.3 (B1), U4#4.1 (AO1), U4#4.2 (AO1)
Board_2-Net-(U1B-B2): U1.4 (B2), U4#4.5 (AO2), U4#4.6 (AO2)
Board_2-Net-(U1C-C1): U1.5 (C1), U2#2.1 (AO1), U2#2.2 (AO1)
Board_2-Net-(U1C-C2): U1.6 (C2), U2#2.5 (AO2), U2#2.6 (AO2)
Board_2-Net-(U1D-D1): U1.7 (D1), U3#2.11 (BO1), U3#2.12 (BO1)
Board_2-Net-(U1D-D2): U1.8 (D2), U3#2.7 (BO2), U3#2.8 (BO2)
Board_2-Net-(U1E-E1): U1.9 (E1), U4#4.11 (BO1), U4#4.12 (BO1)
Board_2-Net-(U1E-E2): U1.10 (E2), U4#4.7 (BO2), U4#4.8 (BO2)
Board_2-Net-(U1F-F1): U1.11 (F1), U2#2.11 (BO1), U2#2.12 (BO1)
Board_2-Net-(U1F-F2): U1.12 (F2), U2#2.7 (BO2), U2#2.8 (BO2)
Board_3-+3.3V: C1#3.1, C2#2.1, C5#3.1, C6#2.1, C9.1, C10#2.1, J7#2.1, U2.15 (PWMB), U2.19 (STBY), U2.20 (VCC), U2.23 (PWMA), U3.15 (PWMB), U3.19 (STBY), U3.20 (VCC), U3.23 (PWMA), U4#3.15 (PWMB), U4#3.19 (STBY), U4#3.20 (VCC), U4#3.23 (PWMA)
Board_3-+7.5V: C3.1, C4#3.1, C7#4.1, C8#3.1, C11.1, C12#4.1, J8.1, U2.13 (VM2), U2.14 (VM3), U2.24 (VM1), U3.13 (VM2), U3.14 (VM3), U3.24 (VM1), U4#3.13 (VM2), U4#3.14 (VM3), U4#3.24 (VM1)
Board_3-A1: J2#3.1, U3.21 (AIN1)
Board_3-A2: J2#3.2, U3.22 (AIN2)
Board_3-B1: J5.1, U4#3.21 (AIN1)
Board_3-B2: J5.2, U4#3.22 (AIN2)
Board_3-C1: J1.1, U2.21 (AIN1)
Board_3-C2: J1.2, U2.22 (AIN2)
Board_3-D1: J4.1, U3.17 (BIN1)
Board_3-D2: J4.2, U3.16 (BIN2)
Board_3-E1: J6#4.1, U4#3.17 (BIN1)
Board_3-E2: J6#4.2, U4#3.16 (BIN2)
Board_3-F1: J3.1, U2.17 (BIN1)
Board_3-F2: J3.2, U2.16 (BIN2)
Board_3-GND: C1#3.2, C2#2.2, C3.2, C4#3.2, C5#3.2, C6#2.2, C7#4.2, C8#3.2, C9.2, C10#2.2, C11.2, C12#4.2, J7#2.2, J8.2, U2.3 (PGND1), U2.4 (PGND1), U2.9 (PGND2), U2.10 (PGND2), U2.18 (GND), U3.3 (PGND1), U3.4 (PGND1), U3.9 (PGND2), U3.10 (PGND2), U3.18 (GND), U4#3.3 (PGND1), U4#3.4 (PGND1), U4#3.9 (PGND2), U4#3.10 (PGND2), U4#3.18 (GND)
Board_3-Net-(U1A-A1): U1#2.1 (A1), U3.1 (AO1), U3.2 (AO1)
Board_3-Net-(U1A-A2): U1#2.2 (A2), U3.5 (AO2), U3.6 (AO2)
Board_3-Net-(U1B-B1): U1#2.3 (B1), U4#3.1 (AO1), U4#3.2 (AO1)
Board_3-Net-(U1B-B2): U1#2.4 (B2), U4#3.5 (AO2), U4#3.6 (AO2)
Board_3-Net-(U1C-C1): U1#2.5 (C1), U2.1 (AO1), U2.2 (AO1)
Board_3-Net-(U1C-C2): U1#2.6 (C2), U2.5 (AO2), U2.6 (AO2)
Board_3-Net-(U1D-D1): U1#2.7 (D1), U3.11 (BO1), U3.12 (BO1)
Board_3-Net-(U1D-D2): U1#2.8 (D2), U3.7 (BO2), U3.8 (BO2)
Board_3-Net-(U1E-E1): U1#2.9 (E1), U4#3.11 (BO1), U4#3.12 (BO1)
Board_3-Net-(U1E-E2): U1#2.10 (E2), U4#3.7 (BO2), U4#3.8 (BO2)
Board_3-Net-(U1F-F1): U1#2.11 (F1), U2.11 (BO1), U2.12 (BO1)
Board_3-Net-(U1F-F2): U1#2.12 (F2), U2.7 (BO2), U2.8 (BO2)

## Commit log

2025-09-04 Remove tracked files except Print_files
2025-09-04 enclosure print files
2025-10-06 uart frame parser and builder added
2025-10-07 arq added
2025-10-21 logic.c overhauled, arduino middleware and minimal frontend added
2025-10-21 handle_reset expanded to restart frame parser and ARQ
2025-10-22 pump parser and inbox fixed, expanded reset and anchor role assignment
2025-10-22 individual uart contexts for ARQ added
2025-10-24 UART test programs and Documentation UMLs
2025-10-24 added BrailleFirmaware readme file
2025-10-24 change Braille_firmware README location
2025-10-24 added exported diagrams
2025-10-24 added images to Braille firmware readme
